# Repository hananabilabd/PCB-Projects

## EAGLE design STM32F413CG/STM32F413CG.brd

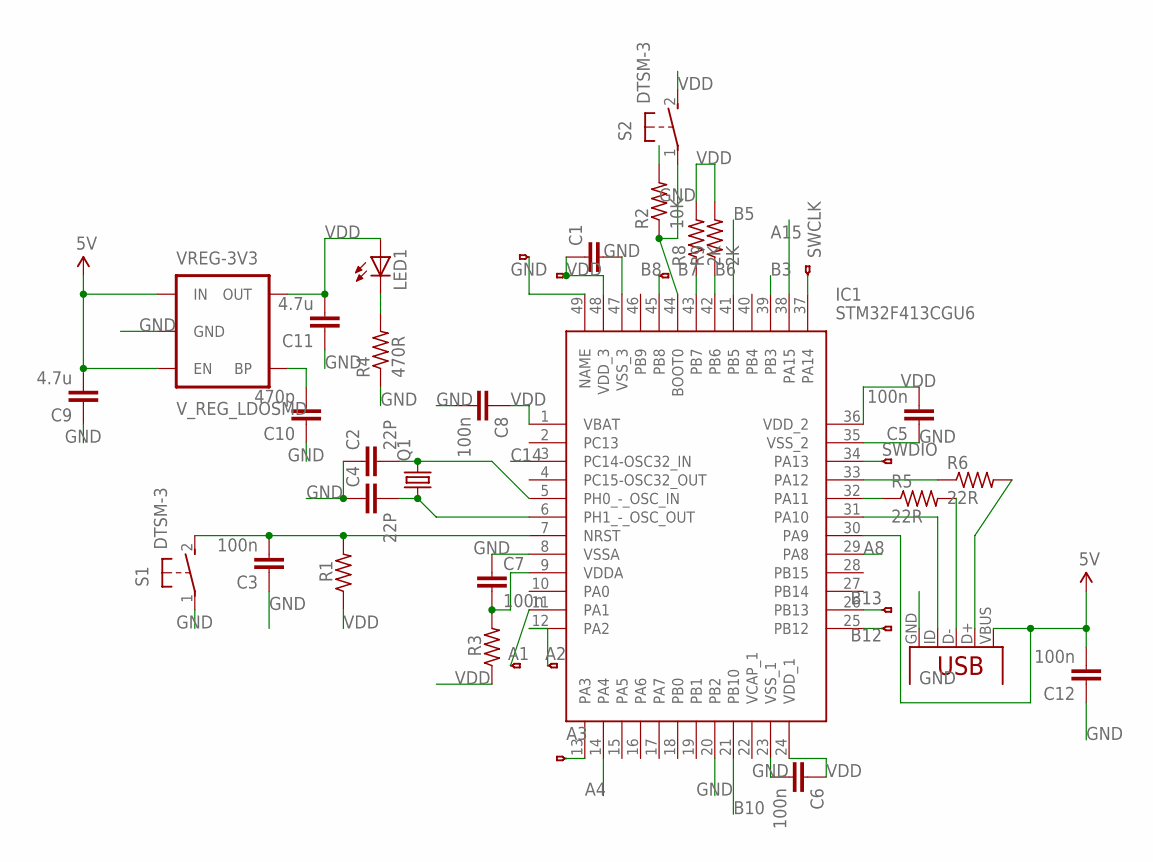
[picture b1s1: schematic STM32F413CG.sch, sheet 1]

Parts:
C1: C2,5-3; C2.5-3
C2, C4: 22P; C2.5-3
C3, C5, C6, C7, C8, C12: 100n; C2.5-3
C9, C11: 4.7u; C2.5-3
C10: 470p; C2.5-3
IC1: STM32F413CGU6; QFN50P700X700X60-49N
JP1, JP2, JP3, JP4, JP5, JP6, JP7, JP8, JP9, JP10: HEADERHOLE-HEADERHOLE; 1X1-HEADER-HOLE
LED1: LED0603; LED-0603
Q1: CRYSTALHC49S; HC49/S
R1, R3: R-US_0204/2V; 0204V
R2: 10K; 0204V
R4: 470R; 0204V
R5, R6: 22R; 0204V
R8, R9: 2K; 0204V
S1, S2: DTSM-3
VREG-3V3: V_REG_LDOSMD; SOT23-5
X1: USB-MICROB-SMD

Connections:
5V: C9.2, C12.2, IC1.30 (PA9), VREG-3V3.1 (IN), VREG-3V3.3 (EN), X1.VBUS
A1: IC1.11 (PA1), JP8.1
A2: IC1.12 (PA2), JP9.1
A3: IC1.13 (PA3), JP10.1
A4: IC1.14 (PA4); also elsewhere on the board
A8: IC1.29 (PA8); also elsewhere on the board
A15: IC1.38 (PA15); also elsewhere on the board
B3: IC1.39 (PB3); also elsewhere on the board
B5: IC1.41 (PB5); also elsewhere on the board
B6: IC1.42 (PB6), R9.1; also elsewhere on the board
B7: IC1.43 (PB7), R8.1; also elsewhere on the board
B8: IC1.45 (PB8), JP5.1
B10: IC1.21 (PB10); also elsewhere on the board
B12: IC1.25 (PB12), JP7.1
B13: IC1.26 (PB13), JP6.1
C14: IC1.3 (PC14-OSC32_IN); also elsewhere on the board
GND: C1.2, C2.1, C3.1, C4.1, C5.1, C6.2, C7.1, C8.2, C9.1, C10.1, C11.1, C12.1, IC1.8 (VSSA), IC1.20 (PB2), IC1.23 (VSS_1), IC1.35 (VSS_2), IC1.47 (VSS_3), IC1.49 (NAME), JP1.1, R2.2, R4.1, S1.1, VREG-3V3.2 (GND), X1.GND; also elsewhere on the board
unnamed: C2.2, IC1.5 (PH0_-_OSC_IN), Q1.2
unnamed: C3.2, IC1.7 (NRST), R1.2, S1.2
unnamed: C10.2, VREG-3V3.4 (BP)
unnamed: C7.2, IC1.9 (VDDA), R3.2
unnamed: LED1.C, R4.2
unnamed: R5.2, X1.D-
unnamed: IC1.31 (PA10), X1.ID
unnamed: IC1.32 (PA11), R5.1
unnamed: R6.2, X1.D+
unnamed: IC1.33 (PA12), R6.1
unnamed: IC1.44 (BOOT0), R2.1, S2.1
unnamed: C4.2, IC1.6 (PH1_-_OSC_OUT), Q1.1
SWCLK: IC1.37 (PA14), JP2.1
SWDIO: IC1.34 (PA13), JP3.1
VCAP_1: IC1.22 (VCAP_1)
VDD: C1.1, C5.2, C6.1, C8.1, C11.2, IC1.1 (VBAT), IC1.24 (VDD_1), IC1.36 (VDD_2), IC1.48 (VDD_3), JP4.1, LED1.A, R1.1, R3.1, R8.2, R9.2, S2.2, VREG-3V3.5 (OUT); also elsewhere on the board

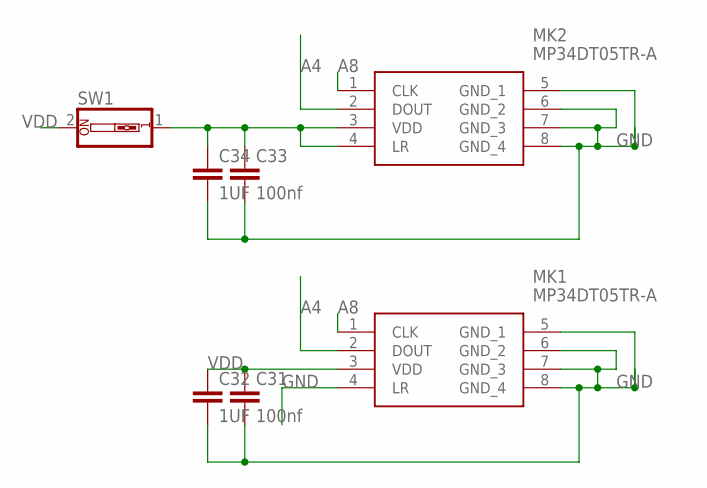
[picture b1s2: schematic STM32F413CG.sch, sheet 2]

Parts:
C31, C33: 100nf; C2.5-2
C32, C34: 1UF; C2.5-2
MK1, MK2: MP34DT05TR-A; MP34DT05TRA
SW1: SW_DIP-1; EDG-01

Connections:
A4: MK1.2 (DOUT), MK2.2 (DOUT); also elsewhere on the board
A8: MK1.1 (CLK), MK2.1 (CLK); also elsewhere on the board
GND: C31.2, C32.2, C33.2, C34.2, MK1.4 (LR), MK1.5 (GND_1), MK1.6 (GND_2), MK1.7 (GND_3), MK1.8 (GND_4), MK2.5 (GND_1), MK2.6 (GND_2), MK2.7 (GND_3), MK2.8 (GND_4); also elsewhere on the board
unnamed: C33.1, C34.1, MK2.3 (VDD), MK2.4 (LR), SW1.1
VDD: C31.1, C32.1, MK1.3 (VDD), SW1.2; also elsewhere on the board

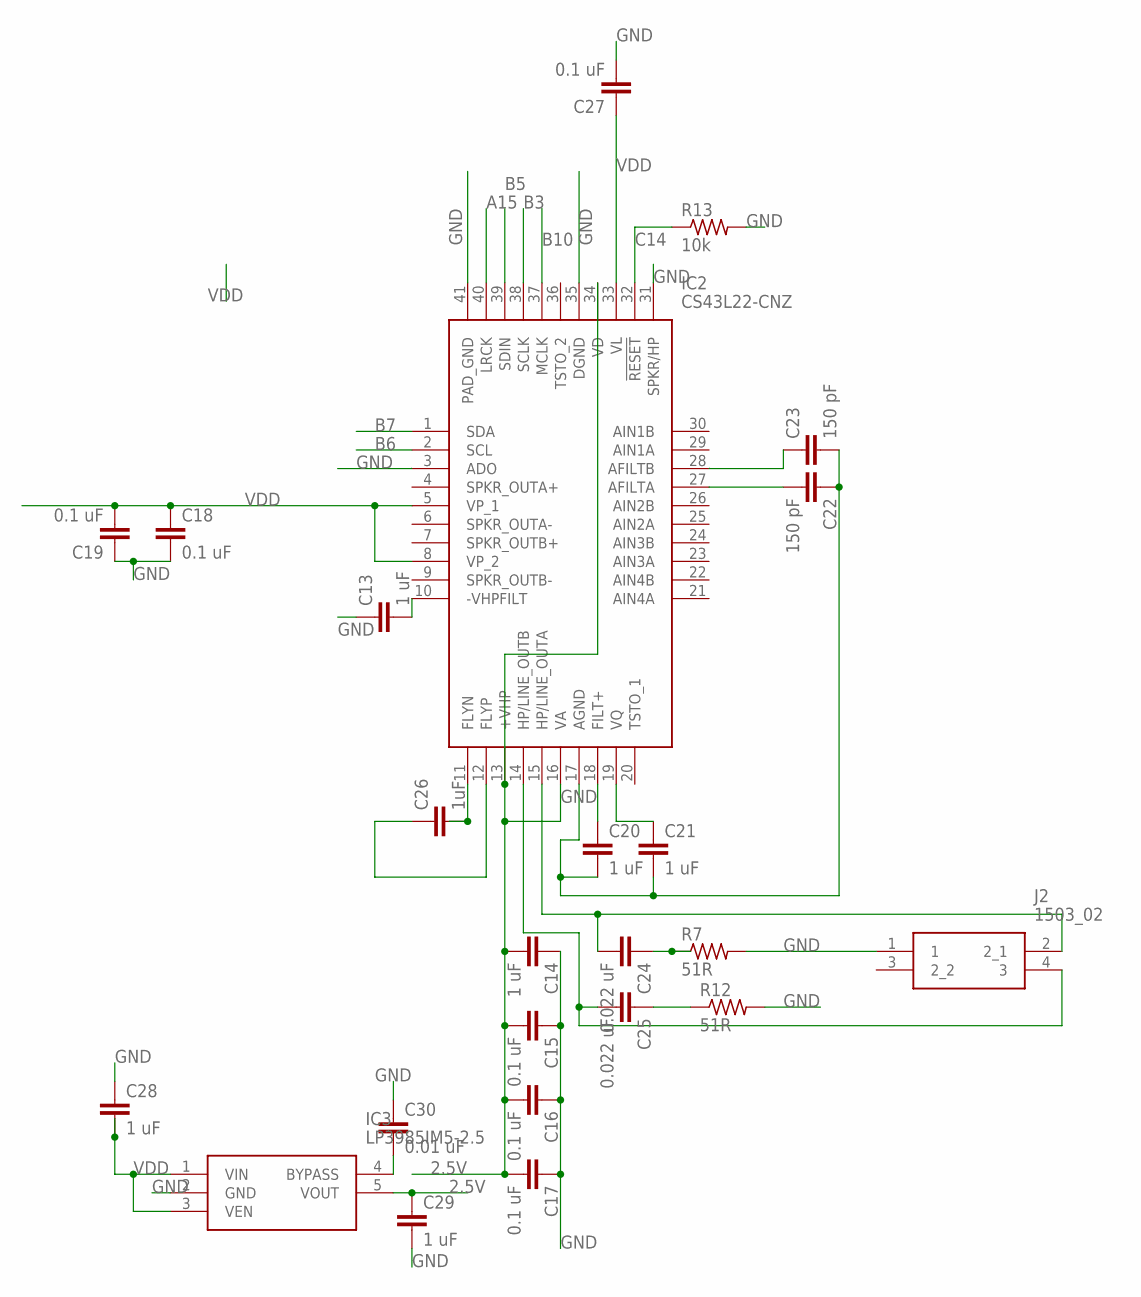
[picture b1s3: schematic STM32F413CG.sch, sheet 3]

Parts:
C13, C14, C20, C21, C28, C29: 1 uF; CAP-PTH-SMALL-KIT
C15, C16, C17, C18, C19, C27: 0.1 uF; CAP-PTH-SMALL-KIT
C22, C23: 150 pF; CAP-PTH-SMALL-KIT
C24, C25: 0.022 uF; CAP-PTH-SMALL-KIT
C26: 1uF; C2.5-3
C30: 0.01 uF; CAP-PTH-SMALL-KIT
IC2: CS43L22-CNZ; QFN50P600X600X100-41N
IC3: LP3985IM5-2.5; SOT95P300X120-5N
J2: 1503_02; 150302
R7, R12: 51R; 0204V
R13: 10k; 0204V

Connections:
2.5V: C14.2, C15.2, C16.2, C17.2, C29.1, IC2.13 (+VHP), IC2.16 (VA), IC2.34 (VD), IC3.5 (VOUT)
A15: IC2.40 (LRCK); also elsewhere on the board
B3: IC2.38 (SCLK); also elsewhere on the board
B5: IC2.39 (SDIN); also elsewhere on the board
B6: IC2.2 (SCL); also elsewhere on the board
B7: IC2.1 (SDA); also elsewhere on the board
B10: IC2.37 (MCLK); also elsewhere on the board
C14: IC2.32 (!RESET), R13.1; also elsewhere on the board
GND: C13.1, C14.1, C15.1, C16.1, C17.1, C18.2, C19.1, C20.2, C21.2, C22.1, C23.2, C27.2, C28.1, C29.2, C30.1, IC2.3 (ADO), IC2.17 (AGND), IC2.31 (SPKR/HP), IC2.35 (DGND), IC2.41 (PAD_GND), IC3.2 (GND), J2.1, R7.2, R12.2, R13.2; also elsewhere on the board
unnamed: C13.2, IC2.10 (-VHPFILT)
unnamed: C26.2, IC2.11 (FLYN)
unnamed: C26.1, IC2.12 (FLYP)
unnamed: C20.1, IC2.18 (FILT+)
unnamed: C21.1, IC2.19 (VQ)
unnamed: C22.2, IC2.27 (AFILTA)
unnamed: C23.1, IC2.28 (AFILTB)
unnamed: C24.2, IC2.15 (HP/LINE_OUTA), J2.2 (2_1)
unnamed: C25.2, IC2.14 (HP/LINE_OUTB), J2.4 (3)
unnamed: C24.1, R7.1
unnamed: C25.1, R12.1
unnamed: C30.2, IC3.4 (BYPASS)
VDD: C18.1, C19.2, C27.1, C28.2, IC2.5 (VP_1), IC2.8 (VP_2), IC2.33 (VL), IC3.1 (VIN), IC3.3 (VEN); also elsewhere on the board

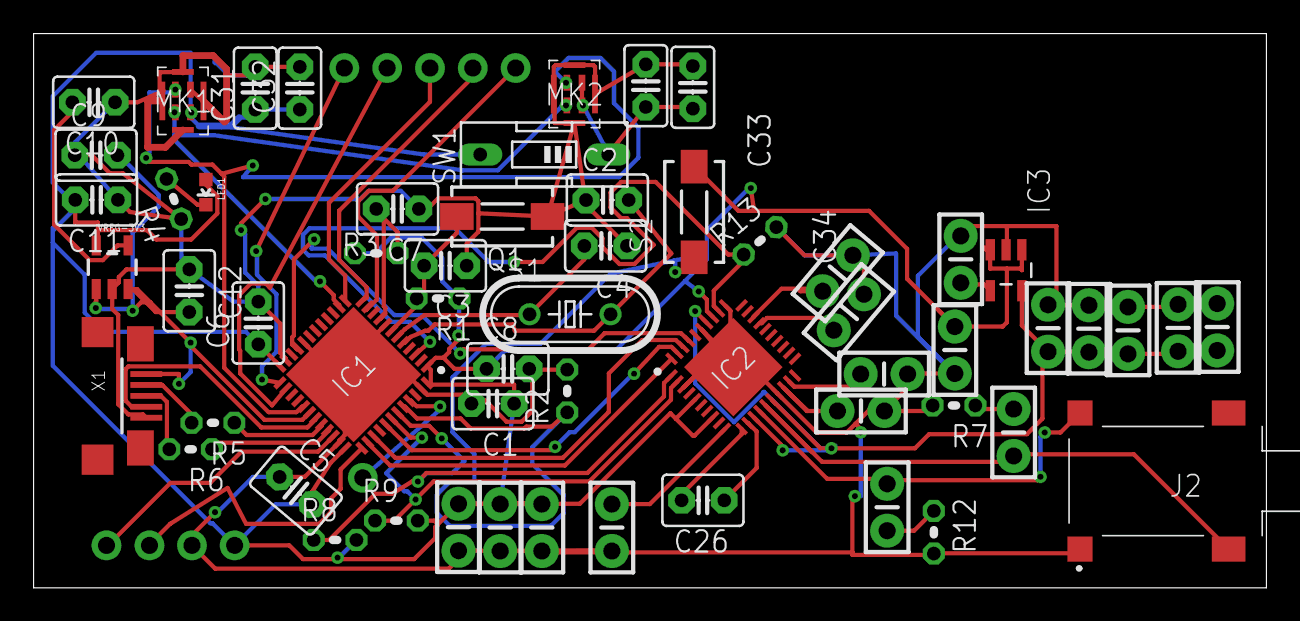
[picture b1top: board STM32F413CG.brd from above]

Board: 2 copper layers, 73.4 x 33.0 mm, 68 parts (0 on the bottom side), 46 nets.

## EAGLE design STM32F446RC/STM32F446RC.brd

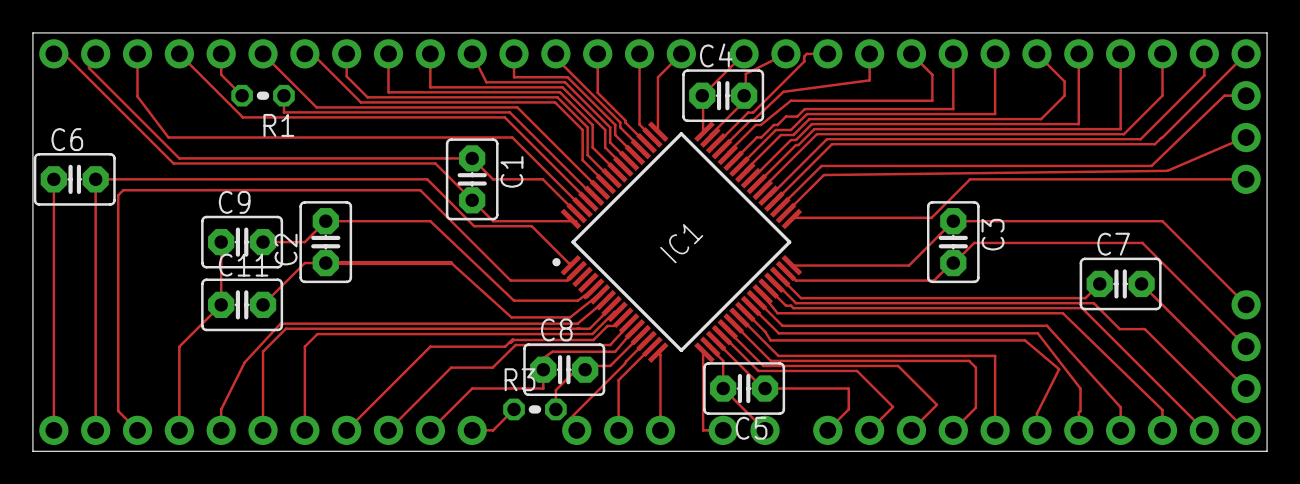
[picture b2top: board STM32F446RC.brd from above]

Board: 2 copper layers, 74.9 x 25.4 mm, 75 parts (0 on the bottom side), 67 nets.

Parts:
C1, C3, C4, C5, C6, C8: 100n+1u; C2.5-3
C2, C9, C11: 20p; C2.5-3
C7: 2.2U; C2.5-3
IC1: STM32F446RCT6; QFP50P1200X1200X160-64N
JP1, JP2, JP3, JP4, JP5, JP6, JP7, JP9, JP10, JP11, JP12, JP13, JP14, JP15, JP16, JP17, JP18, JP19, JP20, JP21, JP22, JP23, JP24, JP25, JP26, JP27, JP28, JP29, JP30, JP31, JP32, JP33, JP34, JP35, JP36, JP37, JP38, JP39, JP40, JP41, JP42, JP43, JP44, JP45, JP46, JP47, JP48, JP49, JP50, JP51, JP52, JP53, JP54, JP55, JP56, JP57, JP58, JP59, JP61, JP62, JP63, JP65: 1X1-HEADER-HOLE
R1: 10k; 0204V
R3: 0204V

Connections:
unnamed: C3.2, IC1.31, JP50.1
unnamed: C8.2, IC1.13, R3.2
unnamed: IC1.7, JP63.1
unnamed: C5.2, IC1.18, JP20.1
unnamed: IC1.60, R1.1
unnamed: C1.2, IC1.64, JP58.1
unnamed: C2.1, C11.2, IC1.6
unnamed: C1.1, IC1.63, JP57.1
unnamed: IC1.59, JP43.1
unnamed: IC1.58, JP42.1
unnamed: IC1.24, JP12.1
unnamed: IC1.25, JP23.1
unnamed: IC1.26, JP22.1
unnamed: IC1.27, JP17.1
unnamed: IC1.28, JP16.1
unnamed: IC1.29, JP14.1
unnamed: IC1.23, JP11.1
unnamed: IC1.22, JP9.1
unnamed: IC1.21, JP19.1
unnamed: IC1.17, JP24.1
unnamed: IC1.33, JP18.1
unnamed: IC1.34, JP13.1
unnamed: IC1.35, JP6.1
unnamed: IC1.36, JP10.1
unnamed: IC1.37, JP1.1
unnamed: IC1.16, JP36.1
unnamed: IC1.15, JP35.1
unnamed: IC1.14, JP34.1
unnamed: IC1.11, JP4.1
unnamed: IC1.10, JP3.1
unnamed: IC1.9, JP27.1
unnamed: IC1.8, JP29.1
unnamed: IC1.2, JP26.1
unnamed: IC1.38, JP15.1
unnamed: IC1.39, JP2.1
unnamed: IC1.40, JP30.1
unnamed: IC1.41, JP28.1
unnamed: IC1.42, JP31.1
unnamed: IC1.43, JP33.1
unnamed: IC1.44, JP32.1
unnamed: IC1.45, JP25.1
unnamed: IC1.57, JP41.1
unnamed: IC1.56, JP40.1
unnamed: IC1.55, JP44.1
unnamed: IC1.54, JP38.1
unnamed: IC1.53, JP39.1
unnamed: IC1.52, JP5.1
unnamed: IC1.51, JP37.1
unnamed: IC1.50, JP45.1
unnamed: IC1.61, JP46.1
unnamed: IC1.62, JP47.1
unnamed: IC1.20, JP21.1
unnamed: C2.2, C9.2, IC1.5
unnamed: C7.2, JP49.1
unnamed: C3.1, IC1.32, JP51.1
unnamed: C4.2, IC1.47, JP52.1
unnamed: JP56.1, R1.2
unnamed: C6.2, IC1.1, JP7.1
unnamed: C8.1, IC1.12, JP62.1
unnamed: JP61.1, R3.1
unnamed: C9.1, C11.1, JP65.1
unnamed: C5.1, IC1.19, JP48.1
unnamed: C7.1, IC1.30
unnamed: C6.1, JP59.1
unnamed: C4.1, IC1.48, JP53.1
SWCLK: IC1.49, JP55.1
SWDIO: IC1.46, JP54.1

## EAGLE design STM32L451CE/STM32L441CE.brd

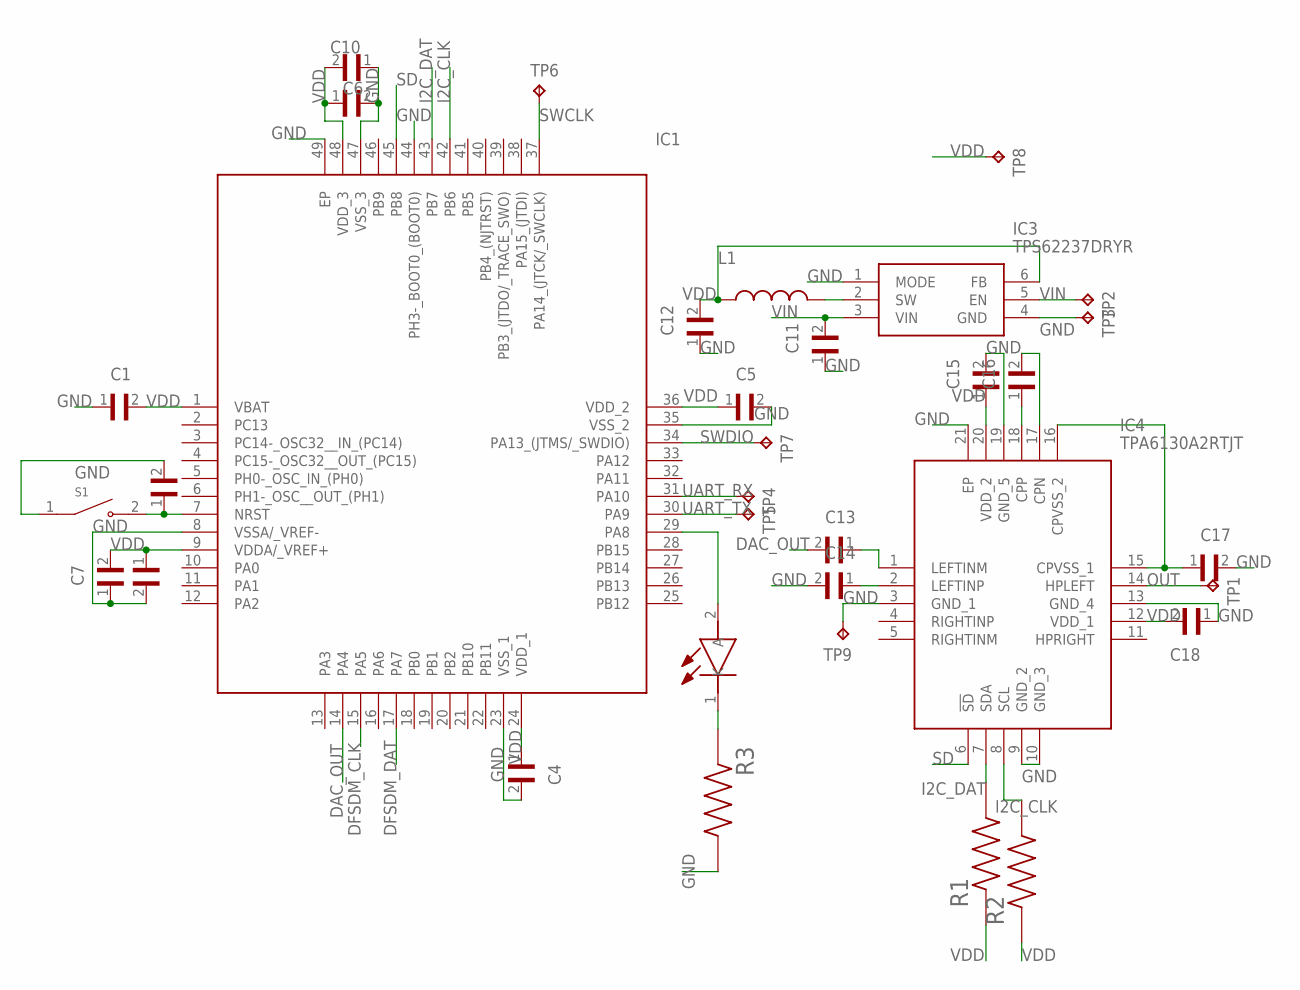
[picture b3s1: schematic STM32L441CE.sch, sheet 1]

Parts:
C1, C2, C3, C4, C5, C6: GRM033C80J104KE15D; CAPC0603X33N
C7, C15, C16, C17, C18: JMK105C6105KV-F; CAPC1005X55N
C10, C12: GRM155R60J475ME47D; CAPC1005X60N
C11: GRM155R60J225KE95D; CAPC1005X55N
C13, C14: CC0402KRX5R5BB474; CAPC1005X55N
IC1: STM32L451CEU6; QFN50P700X700X60-49N
IC3: TPS62237DRYR; SON50P100X145X60-6N
IC4: TPA6130A2RTJT; QFN50P400X400X80-21N
L1: LQM21PN2R2MC0D; INDC2012X55N
LED1: VLMS1500-GS08; VLMG1500GS08
R1, R2, R3: ERJ-1GNJ222C; RESC0603X26N
S1: B3U-1000P; SW_B3U-1000P
TP1, TP2, TP3, TP4, TP5, TP6, TP7, TP8, TP9: TPTP11R; TP11R

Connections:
DAC_OUT: C13.2, IC1.14 (PA4)
DFSDM_CLK: IC1.15 (PA5); also elsewhere on the board
DFSDM_DAT: IC1.17 (PA7); also elsewhere on the board
GND: C1.1, C2.2, C3.2, C4.2, C5.2, C6.2, C7.1, C10.1, C11.1, C12.1, C14.2, C15.2, C17.2, C18.1, IC1.8 (VSSA/_VREF-), IC1.23 (VSS_1), IC1.35 (VSS_2), IC1.44 (PH3-_BOOT0_(BOOT0)), IC1.47 (VSS_3), IC1.49 (EP), IC3.1 (MODE), IC3.4 (GND), IC4.3 (GND_1), IC4.9 (GND_2), IC4.10 (GND_3), IC4.13 (GND_4), IC4.19 (GND_5), IC4.21 (EP), R3.2, S1.1, TP3.TP, TP9.TP; also elsewhere on the board
I2C_CLK: IC1.42 (PB6), IC4.8 (SCL), R2.2
I2C_DAT: IC1.43 (PB7), IC4.7 (SDA), R1.2
unnamed: C2.1, IC1.7 (NRST), S1.2
unnamed: IC3.2 (SW), L1.2
unnamed: C13.1, IC4.1 (LEFTINM)
unnamed: C14.1, IC4.2 (LEFTINP)
unnamed: IC1.29 (PA8), LED1.2 (A)
unnamed: C16.1, IC4.18 (CPP)
unnamed: C16.2, IC4.17 (CPN)
unnamed: C17.1, IC4.15 (CPVSS_1), IC4.16 (CPVSS_2)
unnamed: LED1.1 (K), R3.1
OUT: IC4.14 (HPLEFT), TP1.TP
SD: IC1.45 (PB8), IC4.6 (!SD)
SWCLK: IC1.37 (PA14_(JTCK/_SWCLK)), TP6.TP
SWDIO: IC1.34 (PA13_(JTMS/_SWDIO)), TP7.TP
UART_RX: IC1.31 (PA10), TP4.TP
UART_TX: IC1.30 (PA9), TP5.TP
VDD: C1.2, C3.1, C4.1, C5.1, C6.1, C7.2, C10.2, C12.2, C15.1, C18.2, IC1.1 (VBAT), IC1.9 (VDDA/_VREF+), IC1.24 (VDD_1), IC1.36 (VDD_2), IC1.48 (VDD_3), IC3.6 (FB), IC4.12 (VDD_1), IC4.20 (VDD_2), L1.1, R1.1, R2.1, TP8.TP; also elsewhere on the board
VIN: C11.2, IC3.3 (VIN), IC3.5 (EN), TP2.TP

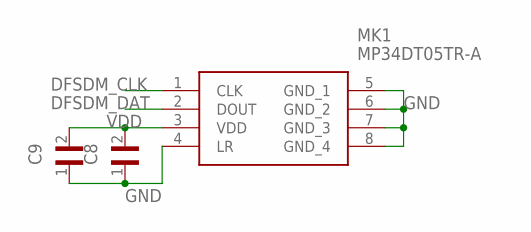
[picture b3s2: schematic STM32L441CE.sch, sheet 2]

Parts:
C8: JMK105C6105KV-F; CAPC1005X55N
C9: GRM033C80J104KE15D; CAPC0603X33N
MK1: MP34DT05TR-A; MP34DT05TRA

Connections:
DFSDM_CLK: MK1.1 (CLK); also elsewhere on the board
DFSDM_DAT: MK1.2 (DOUT); also elsewhere on the board
GND: C8.1, C9.1, MK1.4 (LR), MK1.5 (GND_1), MK1.6 (GND_2), MK1.7 (GND_3), MK1.8 (GND_4); also elsewhere on the board
VDD: C8.2, C9.2, MK1.3 (VDD); also elsewhere on the board

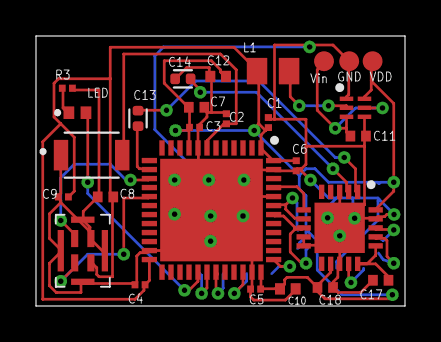
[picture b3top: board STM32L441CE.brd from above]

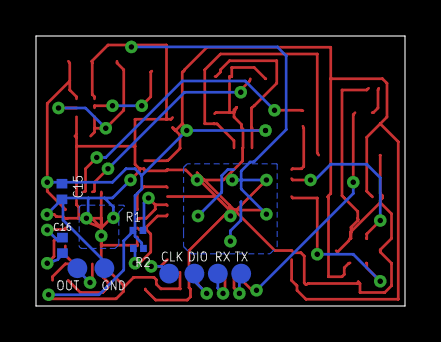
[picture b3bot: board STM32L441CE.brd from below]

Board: 2 copper layers, 20.5 x 15.0 mm, 37 parts (10 on the bottom side), 23 nets.
